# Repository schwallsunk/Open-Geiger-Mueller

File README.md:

# Open Geiger Müller Counter

This repository should provide all the needed parts for the construction of low-cost entry-level Geiger Müller (GM) counter system. This counter was build by request from the students of 151-0163-00L  Nuclear Energy Conversion at ETH Zürich. For a more complete description of the project please read the [manual](https://github.com/schwallsunk/Open-Geiger-Mueller/blob/main/Geiger_counter_manual_final.pdf).

The repository itself is subdivided into two two main parts. The hardware parts contains all the relevant EDA files created in KiCAD v9. The software directory contains all the different code written and tested for and on the hardware.

## The Geiger Müller chamber :radioactive:
The detector is based on either the chinese J321 GM-tube or the soviet SBM-20 GM-tube (can be varied by soldering the negative receptacle either into the spot closer or further away from the HV terminal). The J321 can be easily bought through Aliexpress or ebay whereas for the SBM-20 tube you need to revert to ebay only. 
Due to the overall bigger detection volume of the SBM-20 tube compared with the J321 tube, the sensitivity of the soviet tube will be much higher at the cost of roughly double the price of the J321 tube.

## Microcontroller
The microcontroller of choice here is the Rasperry Pico 2W (rp2350 + wifi chipset), allowing for programming in a multitude of languages (Micropython, Arduino, C++, C), lowering the overall barrier to entry into microcontroller (uC) programming. But the PCB itself also supports the Pico W or any other uC with a fitting pin out. 
The W version of the uC also offers a wireless chip set which supports WiFi as well as Bluetooth connectivity, for which a micropython example is available. This example sends the activity according to the Bluetooth LE standard wirelessly to a receiving device. 
But in case of budgetary concerns, a Rasperry Pico can also be used as a drop-in replacement. The RISC-V-based implementation in this repository might then not work, though.

### Without IDE install
For an easier starting point, there is a precompiled firmware already available in this repository under [FW-file](https://github.com/schwallsunk/Open-Geiger-Mueller/blob/main/software/cpp/Counter_cpp_RISC-V.uf2). This file can be easily flashed by holding down the only button on the Raspberry Pico and plugging it into the USB port of the PC. 
The Pico will then appear as a mass storage device (The button on the Pico can be released at this point ) onto which the given firmware .uf2 file can be dragged and dropped onto it. The microcontroller will reboot by itself as soon as the new firmware file is fully transferred.
From there on, the clicking noise of the background radiation should be heard.

### IDE firmware development
If the goal is to do micropython code development, the following documentation [chapter 4](https://datasheets.raspberrypi.com/pico/raspberry-pi-pico-python-sdk.pdf) might be useful. All the given Micropython examples can be copied and pasted into the IDE and directly deployed. 
For the C/C++ code part, there is either a way to do full code development with the [C/C++ IDE](https://pip-assets.raspberrypi.com/categories/610-raspberry-pi-pico/documents/RP-008276-DS-1-getting-started-with-pico.pdf?disposition=inline), where the given code example can be copied and pasted into the given editor and then, at a later stag,e converted into a binary.  

## Electronics

### Parts sourcing
The sourcing of the components for this project was done entirely through the [LCSC](https://www.lcsc.com/) except for the GM-tube as well as the Raspberry Pico 2W. The GM-tube was bought off [EBAY SBM-20 search](https://www.ebay.com/sch/i.html?_nkw=sbm20&_sacat=0&_from=R40&_trksid=p4624852.m570.l1313) and the Pico 2W can be bought from your local electronics reseller.

### PCB manufacturing
The custom printed circuit board (PCB) itself was produced by sending the relevant gerber files to [JLCPCB](https://www.jlcpcb.com/) and choosing a black finish apart from that there is nothing special to consider when ordering them. The relevant gerber files are all merged into a single zip. This zip can be found in the hardware part of this repository.

### BOM 
| LCSC part number | Part description                                          | Amount | Price per piece (USD/piece) | Label of Part on PCB                    |
|------------------|-----------------------------------------------------------|--------|-----------------------------|----------------------------------------|
| C252915          | 2.048kHz 3.3V Electromagnetic Through Hole Buzzer         | 1      | 0.1854                      | BZ1                                    |
| C49234238        | Through Hole Pushbutton Switches RoHS                     | 4      | 0.0809                      | SW1, SW2, SW3, SW4                     |
| C2894588         | Carbon Film Resistor 300Ω                                 | 1      | 0.0043                      | R2                                     |
| C122827          | Metal Film Resistor 22Ω 3W                                | 1      | 0.0392                      | R1                                     |
| C2686215         | 10nF -40°C~+110°C ±5% 1kV)                                | 1      | 0.0969                      | C1                                     |
| C714352          | Carbon Film Resistor 10kΩ 500mW                           | 6      | 0.0081                      | R6,R8,R10,R11,R12,R13                  |
| C142864          | Cylindrical Clip Through Hole,P=7.6mm Fuseholders RoHS    | 2      | 0.1619                      | HV POS (+) and either J321 or SBM-20   |
| C20613339        | 20mA 5 mm flat-head LED                                   | 1      | 0.1041                      | D5                                     |
| C433559          | Metal Film Resistor 22kΩ 3W                               | 1      | 0.0549                      | R4                                     |
| C5156722         | 40V 625mW 200mA NPN TO-92 Single Bipolar Transistors RoHS | 1      | 0.0391                      | Q2                                     |
| C30190409        | Glass Glaze Resistor 4.7MΩ                                | 1      | 0.0553                      | R3                                     |
| C2924242         | 100mA 10mH ±10% Drum-core inductor                        | 1      | 0.173                       | L1                                     |
| C152300          | 30A 175ns 600V 1V@1A 1A DO-41 Single Diodes RoHS          | 1      | 0.0655                      | D1 => look at polarity when installing |
| C256388          | 400V 2.1W 1.5A NPN TO-92 Single Bipolar Transistors RoHS  | 1      | 0.1451                      | Q1                                     |
| C122214          | 100kΩ 1W ±250ppm/°C                                       | 1      | 0.0923                      | R5                                     |
| C7499336         | Pin header 2.54mm 20P                                     | 2      | 0.1601                      | A1 both rows                           |
| C434407          | 220pF capacitor                                           | 1      | 0.2914                      | C2                                     |

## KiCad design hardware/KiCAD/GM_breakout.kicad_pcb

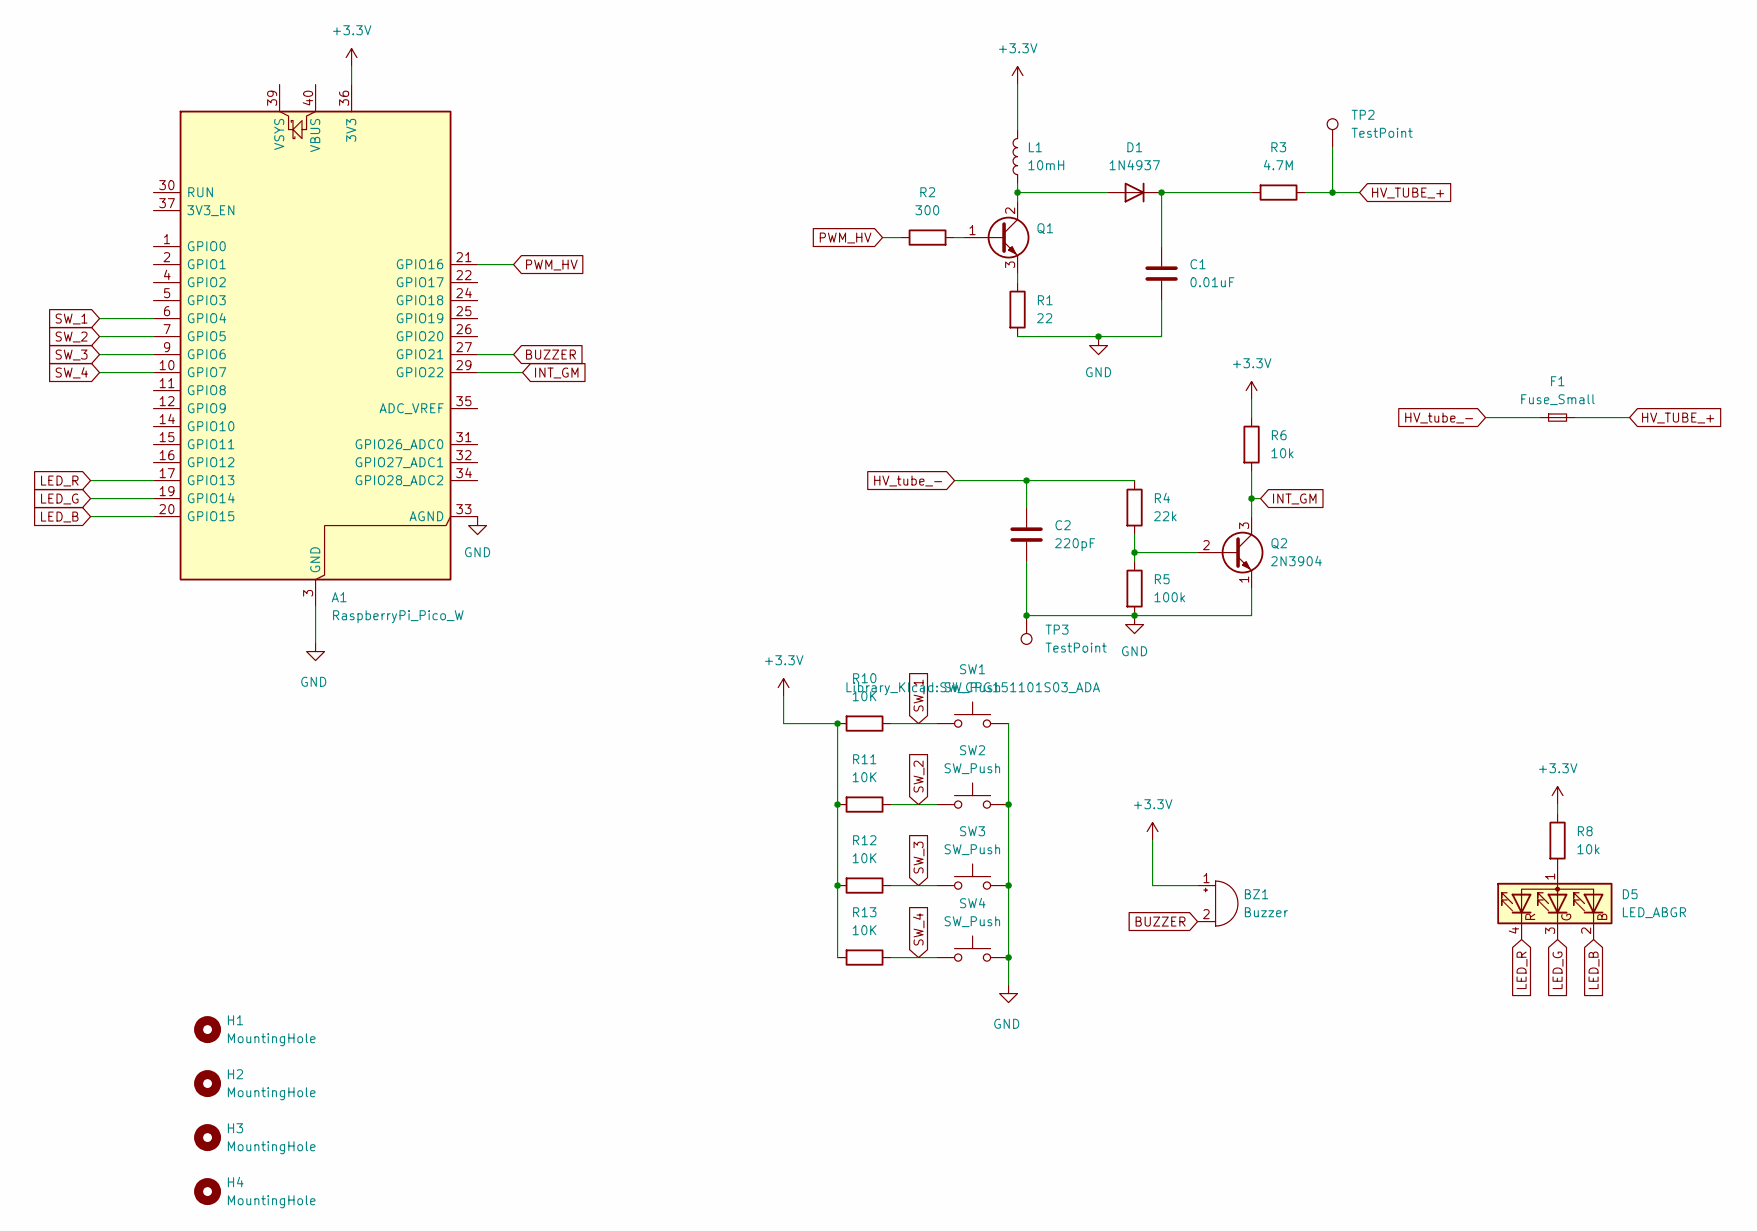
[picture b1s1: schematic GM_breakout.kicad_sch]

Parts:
A1: RaspberryPi_Pico_W; RaspberryPi_Pico_Common_Unspecified
BZ1: Buzzer; Buzzer_TDK_PS1240P02BT_D12.2mm_H6.5mm
C1: 0.01uF; C_Rect_L11.0mm_W6.3mm_P10.00mm_MKT
C2: 220pF; C_Rect_L16.5mm_W7.3mm_P15.00mm_MKT
D1: 1N4937; D_DO-41_SOD81_P10.16mm_Horizontal
D5: LED_ABGR; LED_D5.0mm-4_RGB
F1: Fuse_Small; SBM-20_GM_holder
H1, H2, H3, H4: MountingHole; MountingHole_3.2mm_M3_ISO14580
L1: 10mH; L_Radial_D9.5mm_P5.00mm_Fastron_07HVP
Q1: MJE13003; TO-92_Inline_Wide
Q2: 2N3904; TO-92_Inline_Wide
R1: 22; R_Axial_DIN0516_L15.5mm_D5.0mm_P20.32mm_Horizontal
R2: 300; R_Axial_DIN0207_L6.3mm_D2.5mm_P10.16mm_Horizontal
R3: 4.7M; R_Axial_DIN0411_L9.9mm_D3.6mm_P15.24mm_Horizontal
R4: 22k; R_Axial_DIN0516_L15.5mm_D5.0mm_P20.32mm_Horizontal
R5: 100k; R_Axial_DIN0414_L11.9mm_D4.5mm_P20.32mm_Horizontal
R6, R8: 10k; R_Axial_DIN0309_L9.0mm_D3.2mm_P15.24mm_Horizontal
R10, R11, R12, R13: 10K; R_Axial_DIN0309_L9.0mm_D3.2mm_P15.24mm_Horizontal
SW1, SW2, SW3, SW4: SW_Push; SW_CPG151101S03_ADA
TP2, TP3: TestPoint; TestPoint_Loop_D2.50mm_Drill1.0mm

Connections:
+3.3V: A1.36 (3V3), BZ1.1 (+), L1.2, R6.1, R8.1, R10.2, R11.2, R12.2, R13.2
BUZZER: A1.27 (GPIO21), BZ1.2 (-)
GND: A1.3 (GND), A1.8 (GND), A1.13 (GND), A1.18 (GND), A1.23 (GND), A1.28 (GND), A1.33 (AGND), A1.38 (GND), C1.2, C2.2, Q2.1 (E), R1.2, R5.2, SW1.2, SW2.2, SW3.2, SW4.2, TP3.1
HV_TUBE_+: F1.2, R3.1, TP2.1
HV_tube_-: C2.1, F1.1, R4.1
INT_GM: A1.29 (GPIO22), Q2.3 (C), R6.2
LED_B: A1.20 (GPIO15), D5.2 (BK)
LED_G: A1.19 (GPIO14), D5.3 (GK)
LED_R: A1.17 (GPIO13), D5.4 (RK)
unnamed: D1.2 (A), L1.1, Q1.2 (C)
unnamed: C1.1, D1.1 (K), R3.2
unnamed: D5.1 (A), R8.2
unnamed: Q1.1 (B), R2.2
unnamed: Q1.3 (E), R1.1
unnamed: Q2.2 (B), R4.2, R5.1
PWM_HV: A1.21 (GPIO16), R2.1
SW_1: A1.6 (GPIO4), R10.1, SW1.1
SW_2: A1.7 (GPIO5), R11.1, SW2.1
SW_3: A1.9 (GPIO6), R12.1, SW3.1
SW_4: A1.10 (GPIO7), R13.1, SW4.1

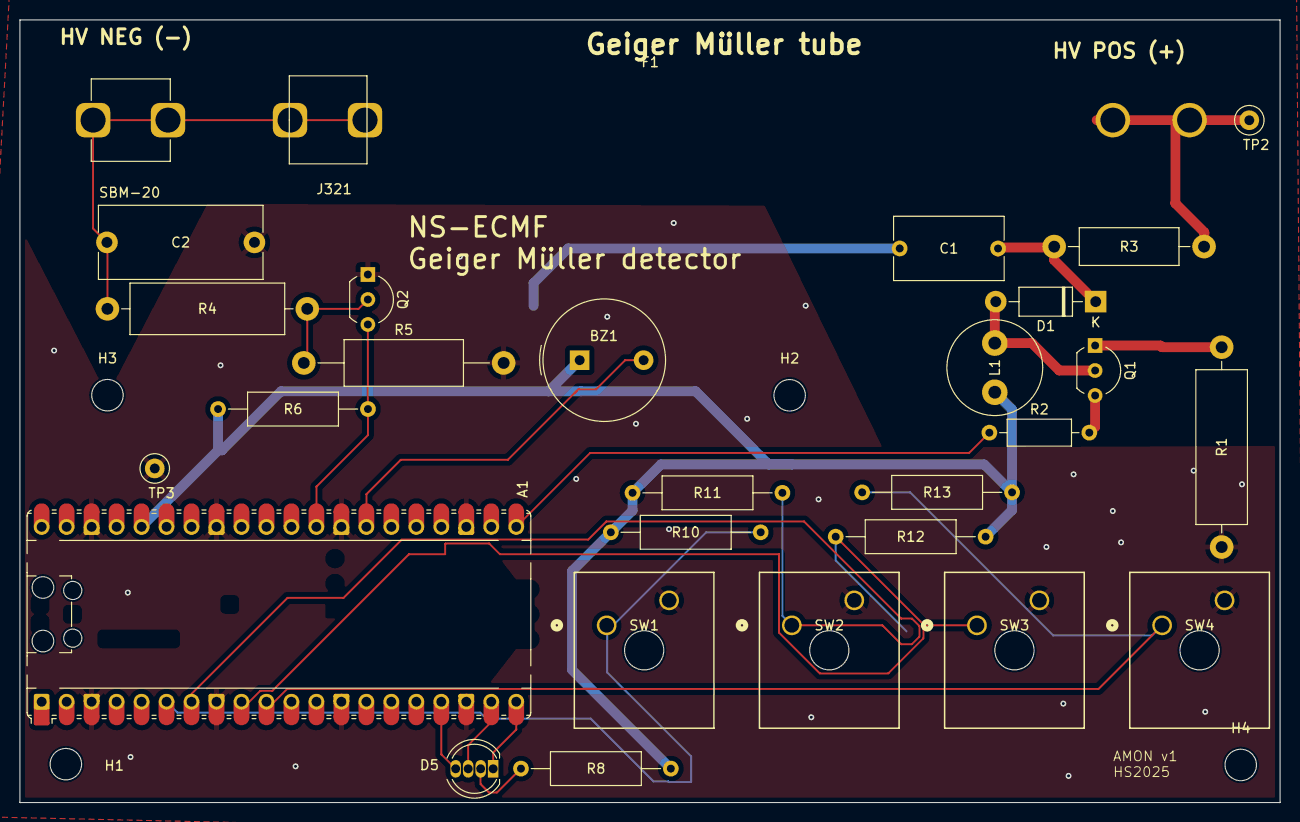
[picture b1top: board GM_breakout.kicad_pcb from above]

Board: 2 copper layers, 128.1 x 79.6 mm, 31 parts (0 on the bottom side), 20 nets.

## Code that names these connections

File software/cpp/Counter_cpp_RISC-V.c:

// __author__ = "Saioul Ngoun and Axel Monney"
// __copyright__ = "Copyright 2025, Open Geiger Mueller project"
// __license__ = "GPL"
// __version__ = "1.0.0"
// __status__ = "Production"




#include <stdio.h>
#include "pico/stdlib.h"
#include "hardware/timer.h"
#include "hardware/gpio.h"
#include "hardware/pwm.h"

const uint16_t PERIOD_INTEGRATION_COUNTS = 1000U;  // Interrupt period in ms within which the counts are being averaged for
const uint8_t HV_TUBE_INT_PIN = 22U; // Geiger tube interrupt for ionization counting
const uint8_t HV_TUBE_PSU_PIN = 16U; // HV tube high voltage (HV) switching power supply stimulus pin
const uint8_t BUZZER_PIN = 21U; // Pin on which Piezo buzzer is hooked up to
const uint8_t LED_R_PIN = 13U; // Pin for the red color of the RGB LED
const uint8_t LED_G_PIN = 14U; // Pin for the green color of the RGB LED
const uint8_t LED_B_PIN = 15U; // Pin for the blue color of the RGB LED
const uint8_t SWITCH_1_PIN = 4U; // Pin for the switch 1 labelled SW1 on PCB
const uint8_t SWITCH_2_PIN = 5U; // Pin for the switch 2 labelled SW2 on PCB 
const uint8_t SWITCH_3_PIN = 6U; // Pin for the switch 3 labelled SW3 on PCB
const uint8_t SWITCH_4_PIN = 7U; // Pin for the switch 4 labelled SW4 on PCB 

uint16_t counts_array_moving_avg[10]; // Moving window array for averaged cps value
volatile uint16_t counter = 0;
volatile bool Buzzer_state = 0;
static repeating_timer_t timer; // struct used for the repeating measurement timer interrupt
volatile bool Flag_thread_lock = false;
volatile uint8_t counter_location = 0;

void counter_callback(){
    irq_set_enabled(IO_IRQ_BANK0,false);
    counter++;
    Buzzer_state = !Buzzer_state;
    gpio_put(BUZZER_PIN,Buzzer_state);
    irq_set_enabled(IO_IRQ_BANK0,true);
}

void print_measurements(uint16_t *buf,
                const uint size_buf){
  for(uint i=0; i<size_buf;i++){
    printf("%u,",*(buf+i));
    }
  printf("\n");
}

void print_bequerel(uint16_t *buf,
                const uint size_buf){
    uint32_t total_count = 0;
    double total_activity = 0.;
    for(uint i=0; i<size_buf;i++){
    total_count=*(buf+i)+total_count;
    }
    total_activity = total_count/(size_buf*(PERIOD_INTEGRATION_COUNTS/1000));
    printf("The total acitvity in of the sample is %e Bq",total_activity);
    printf("\n");
    printf("The total amount of decays in of the sample over the last 10 seconds are %u decays",total_count);
    printf("\n");
    }

bool alarm_callback(repeating_timer_t *t) {
    if (counter_location < 10){
        counter_location++;
        counts_array_moving_avg[counter_location] = counter;
    }
    else{
        counts_array_moving_avg[0] = counter;
        counter_location = 0;
    }
    counter = 0;
    return true;
}

int main()
{
    stdio_init_all();

    // Setup of all GPIOs
    gpio_set_irq_callback(&counter_callback);
    gpio_set_irq_enabled(HV_TUBE_INT_PIN, GPIO_IRQ_EDGE_FALL, true);
    gpio_init(BUZZER_PIN); gpio_set_dir(BUZZER_PIN, GPIO_OUT);gpio_put(BUZZER_PIN,1);
    gpio_set_function(HV_TUBE_PSU_PIN, GPIO_FUNC_PWM);
    uint slice_num = pwm_gpio_to_slice_num(HV_TUBE_PSU_PIN); // find out to which slice Pin16 is connected to => should be slice 0
    pwm_set_wrap(slice_num, 25000); // Setting period lenght in clock cycles here for cpu clocked at 150MHz
    pwm_set_chan_level(slice_num, 0, 21500); // When to break circuit 
    pwm_set_enabled(slice_num, true);
    printf("HV is on!\n");
    gpio_init(LED_R_PIN); gpio_set_dir(LED_R_PIN, GPIO_OUT);gpio_put(LED_R_PIN,0);
    gpio_init(LED_G_PIN); gpio_set_dir(LED_G_PIN, GPIO_OUT);gpio_put(LED_G_PIN,0);
    gpio_init(LED_B_PIN); gpio_set_dir(LED_B_PIN, GPIO_OUT);gpio_put(LED_B_PIN,1);
    gpio_init(SWITCH_1_PIN); gpio_set_dir(SWITCH_1_PIN, GPIO_IN);gpio_pull_up(SWITCH_1_PIN);
    gpio_init(SWITCH_2_PIN); gpio_set_dir(SWITCH_2_PIN, GPIO_IN);gpio_pull_up(SWITCH_2_PIN);
    gpio_init(SWITCH_3_PIN); gpio_set_dir(SWITCH_3_PIN, GPIO_IN);gpio_pull_up(SWITCH_3_PIN);
    gpio_init(SWITCH_4_PIN); gpio_set_dir(SWITCH_4_PIN, GPIO_IN);gpio_pull_up(SWITCH_4_PIN);
    gpio_init(HV_TUBE_INT_PIN); gpio_set_dir(HV_TUBE_INT_PIN, GPIO_IN);gpio_pull_up(SWITCH_4_PIN);
    irq_set_enabled(IO_IRQ_BANK0,true);
    add_repeating_timer_ms(PERIOD_INTEGRATION_COUNTS, alarm_callback, NULL, &timer);

    while (true) {
        if(!gpio_get(SWITCH_1_PIN)){
        print_measurements(counts_array_moving_avg,10);
        sleep_ms(1000);
        }
        if(!gpio_get(SWITCH_2_PIN)){
        print_bequerel(counts_array_moving_avg,10);
        sleep_ms(1000);
        }
        tight_loop_contents();
    }
    cancel_repeating_timer (&timer);
}

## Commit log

2025-11-10 Update LICENSE
2025-11-18 first push and structuring
2025-11-23 C-code
    Added low level RISC-V based code
2026-06-29 Update README with project manual link
    Added a link to the project manual for more information.
